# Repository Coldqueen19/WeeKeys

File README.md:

# WeeKeys

## Pathfinder Session 1 - [40 minutes]
I installed kicad, kicad wakatime, and created my project

## Pathfinder Session 2 - [40 minutes]

I created my schematic for the PCB.

## Pathfinder Session 3 - [40 minutes]

I created the PCB layout and started coding.

## Pathfinder Session 4 - [2 hours]

Finished coding

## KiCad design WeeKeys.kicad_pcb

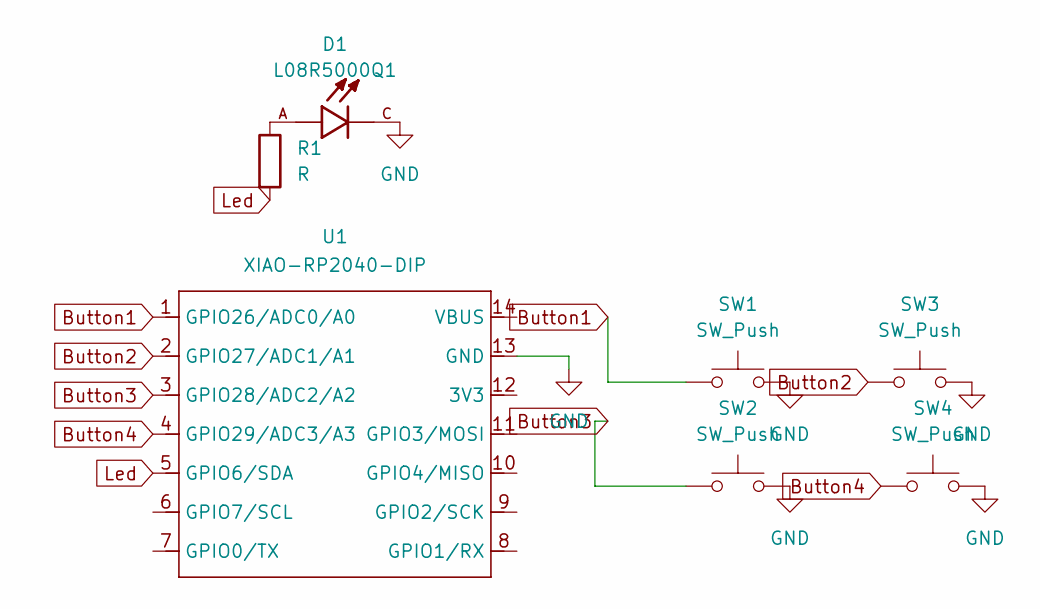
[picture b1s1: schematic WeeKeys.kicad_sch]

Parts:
D1: L08R5000Q1; LEDRD254W57D500H1070; PARTREV NA
R1: R; R_Axial_DIN0204_L3.6mm_D1.6mm_P5.08mm_Horizontal
SW1, SW2, SW3, SW4: SW_Push; SW_Cherry_MX_1.00u_PCB
U1: XIAO-RP2040-DIP; XIAO-RP2040-DIP (2)

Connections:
Button1: SW1.1, U1.1 (GPIO26/ADC0/A0)
Button2: SW3.1, U1.2 (GPIO27/ADC1/A1)
Button3: SW2.1, U1.3 (GPIO28/ADC2/A2)
Button4: SW4.1, U1.4 (GPIO29/ADC3/A3)
GND: D1.C, SW1.2, SW2.2, SW3.2, SW4.2, U1.13 (GND)
Led: R1.2, U1.5 (GPIO6/SDA)
unnamed: D1.A, R1.1

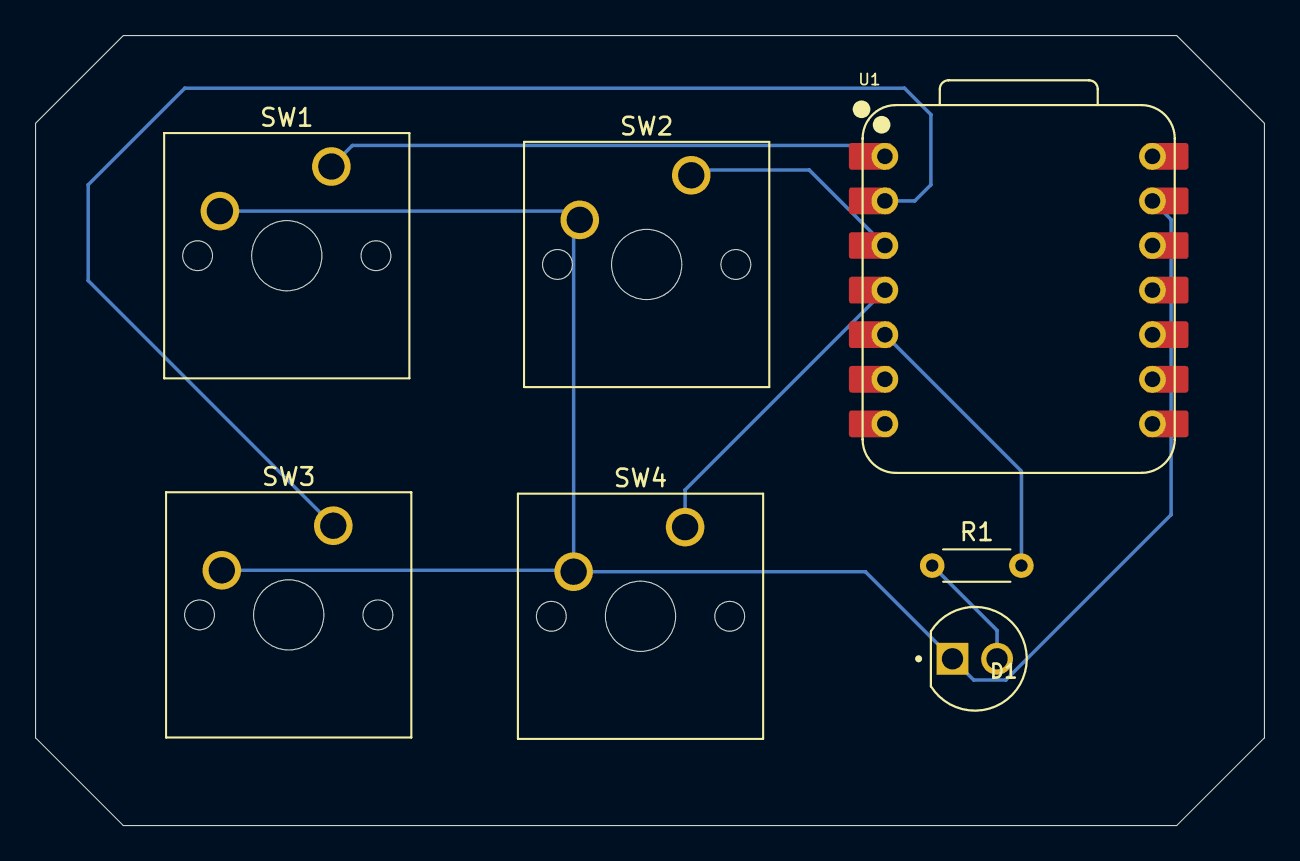
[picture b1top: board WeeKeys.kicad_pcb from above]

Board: 2 copper layers, 70.0 x 45.0 mm, 7 parts (0 on the bottom side), 7 nets.
